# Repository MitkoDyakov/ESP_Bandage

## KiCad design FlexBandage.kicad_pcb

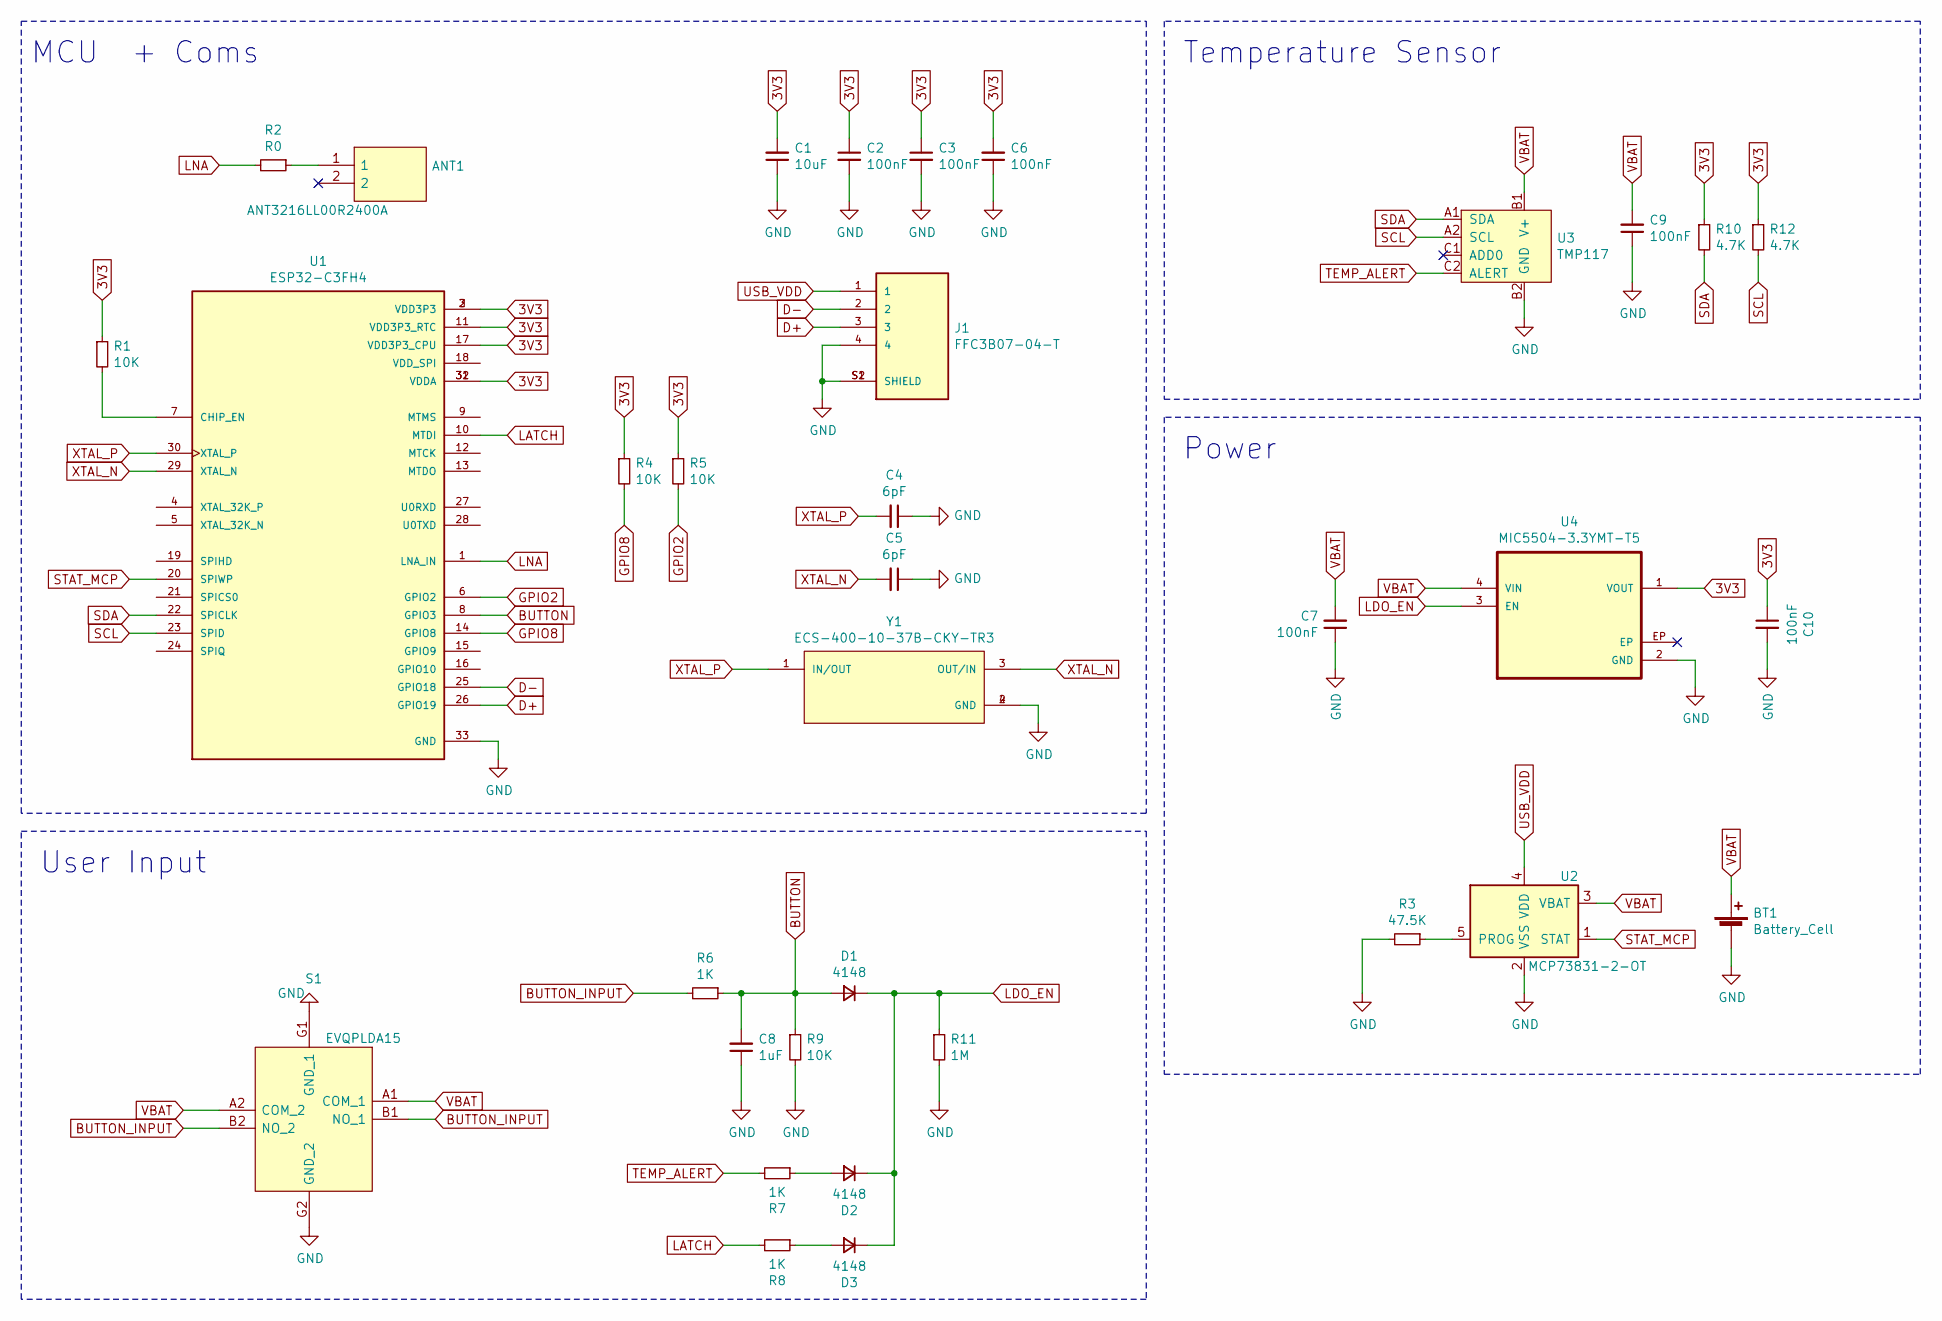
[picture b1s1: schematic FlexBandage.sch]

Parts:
ANT1: ANT3216LL00R2400A
BT1: Battery_Cell; PinHeader_1x02_P1.00mm_Vertical
C1: 10uF; C_0402_1005Metric
C2, C3, C6, C7, C9, C10: 100nF; C_0402_1005Metric
C4, C5: 6pF; C_0402_1005Metric
C8: 1uF; C_0402_1005Metric
D1, D2, D3: 4148; D_SOD-523
J1: FFC3B07-04-T; GCT_FFC3B07-04-T
R1, R4, R5, R9: 10K; R_0402_1005Metric
R2: R0; R_0402_1005Metric
R3: 47.5K; R_0402_1005Metric
R6, R7, R8: 1K; R_0402_1005Metric
R10, R12: 4.7K; R_0402_1005Metric
R11: 1M; R_0402_1005Metric
S1: EVQPLDA15
U1: ESP32-C3FH4; ESP
U2: MCP73831-2-OT; SOT-23-5
U3: TMP117; BGA6N40P3X2_146X96X50N
U4: MIC5504-3.3YMT-T5; VREG_MIC5504-3.3YMT-TZ
Y1: ECS-400-10-37B-CKY-TR3; XTAL_ECS-160-9-37-CKM-TR

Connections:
3V3: C1.2, C2.1, C3.1, C6.2, C10.1, R1.1, R4.1, R5.1, R10.1, R12.1, U1.2 (VDD3P3), U1.3 (VDD3P3), U1.11 (VDD3P3_RTC), U1.17 (VDD3P3_CPU), U1.31 (VDDA), U1.32 (VDDA), U4.1 (VOUT)
BUTTON: C8.2, D1.2 (A), R6.1, R9.1, U1.8 (GPIO3)
BUTTON_INPUT: R6.2, S1.B1 (NO_1), S1.B2 (NO_2)
D+: J1.3, U1.26 (GPIO19)
D-: J1.2, U1.25 (GPIO18)
GND: BT1.2 (-), C1.1, C2.2, C3.2, C4.1, C5.1, C6.1, C7.1, C8.1, C9.1, C10.2, J1.4, J1.S1 (SHIELD), J1.S2 (SHIELD), R3.2, R9.2, R11.2, S1.G1 (GND_1), S1.G2 (GND_2), U1.33 (GND), U1.34, U1.35, U1.36, U1.40, U1.43, U1.47, U1.49, U1.e48, U2.2 (VSS), U3.B2 (GND), U4.2 (GND), Y1.2 (GND), Y1.4 (GND)
GPIO2: R5.2, U1.6 (GPIO2)
GPIO8: R4.2, U1.14 (GPIO8)
LATCH: R8.2, U1.10 (MTDI)
LDO_EN: D1.1 (K), D2.1 (K), D3.1 (K), R11.1, U4.3 (EN)
LNA: R2.2, U1.1 (LNA_IN)
unnamed: ANT1.1, R2.1
unnamed: D2.2 (A), R7.1
unnamed: D3.2 (A), R8.1
unnamed: R1.2, U1.7 (CHIP_EN)
unnamed: R3.1, U2.5 (PROG)
SCL: R12.2, U1.23 (SPID), U3.A2 (SCL)
SDA: R10.2, U1.22 (SPICLK), U3.A1 (SDA)
STAT_MCP: U1.20 (SPIWP), U2.1 (STAT)
TEMP_ALERT: R7.2, U3.C2 (ALERT)
USB_VDD: J1.1, U2.4 (VDD)
VBAT: BT1.1 (+), C7.2, C9.2, S1.A1 (COM_1), S1.A2 (COM_2), U2.3 (VBAT), U3.B1 (V+), U4.4 (VIN)
XTAL_N: C5.2, U1.29 (XTAL_N), Y1.3 (OUT/IN)
XTAL_P: C4.2, U1.30 (XTAL_P), Y1.1 (IN/OUT)

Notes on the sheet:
Temperature Sensor
MCU + Coms
User Input
Power

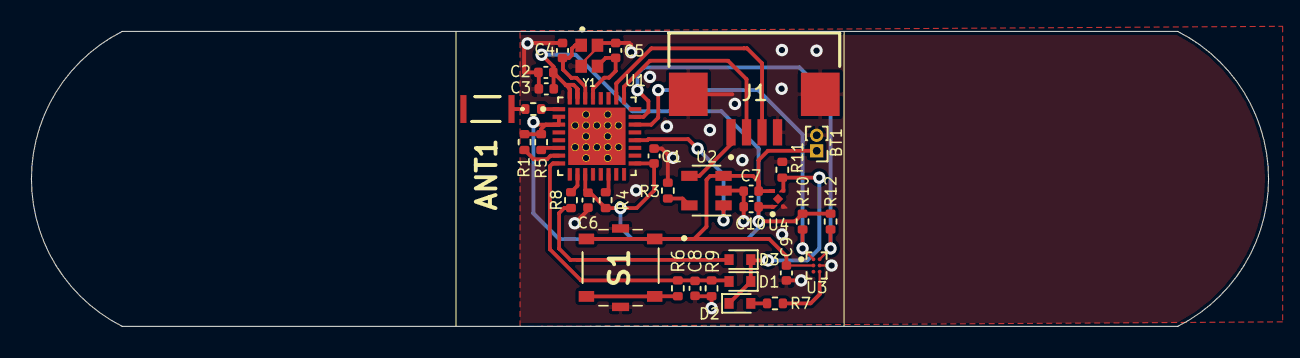
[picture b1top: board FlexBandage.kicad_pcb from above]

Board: 2 copper layers, 79.7 x 19.0 mm, 34 parts (0 on the bottom side), 24 nets.

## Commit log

2024-01-05 initial submit
2024-01-06 update badge
